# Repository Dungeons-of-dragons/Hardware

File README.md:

# Hardware

This repo holds our PCB schematics and PCB design and is used for version control of PCBs.

## PCB design directory

The directory holds the **Project_Libraries** and schematics and PCB design.

Thr Project Libraries folder contains custom symbols and footprints of the sensors used. The component used can be found within the Home.csv file. that is the BOM.

## Bill of Materials

The components needed to replicate this PCB and project are:

- 1 ESP32 DEVKIT V1 microcontroller
- 2 LM2596 Buck converters
- 1 Buzzer
- 1 RGB LED (or three  LEDs, note to add resistors if used)
- 7 2-pin screw terminal blocks
- 2 3-pin screw terminal blocks
- 1 ACS712_5B sensor (current sensor)
- 1 DHT11 sensor (Temperature and Humidity)
- 1 PIR sensor (motion sensor)
- 1 MQ2 sensor (gas sensor)
- 1 Relay

There are components attatched to the PCB externally:

- 1 Fan
- 1 LCD with I2C
- 1 EM Lock
- 1  RFID card reader (RFC522)
- 12V power supply
- 1 Relay module

## The PCB Schematic

### Power Distribution

Components used had different power needs. The use of two buck converters is to ensure that the components that were powered by 3.3V, 5V and 12V are catered for.
An external power source of 12V is used to power the PCB through the power terminal that is the power input of the PCB. Power is the distributed from there.

### External connections

Terminals are used as input and output to components used externally such as the RFID card reader, Electromagnetic lock, fan and LCD. The ACS terminal is used as input of the voltage to be measured by the ACS712 sensor.

## PCB

### Layers of the PCB

Courtyard - Boundary of a footprint.
Fab - Stands for . It gives more information on fabrication to the manufacturer.
Adhesive - Layer to glue components that need to be put in place.
Paste - Layer to apply solder mask onto a PCB.
Silkscreen - Layer to label components and print onto.
Mask - Protects the PCB circuit adn insulates the copper from oxidation.
Copper layer - where copper routes are made and grounding places are set.

As we were fabricating ourselves, some of the layers were not needed, such as mask, fab. adhesive.

### Constraints set up

1. Minimum clearance - this is the minimum distance between 2 tracks. Too small of clearance and tracks might end up being short circuited. 0.15 is the standard requirement for the PCB.
2. Track width - this refers to the thickness of tracks. Small tracks may cause open circuits in the PCB and therefore is discouraged. The amount of current drawn by the components is a factor that should be considered. however, overall, 0.15 is good practice. The power tracks and signal tracks have different sizes due to the amount of current drawn. The 12V power tracks are thicker as they carry more current compared to ther other tracks.
3. Minimum connection width - this refers to the minimum connection between 2 components of the width is less than threshold, connection may be broken.
Kicad provides a track width calculator, we set the 12V tracks to carry 1A of current and the other tracks carrying less that 1A.

4. Minimum through hole - This is the minimum diameter of a trhough hole pin. 0.8 is set because the least strongest drill bit we can use without breaking is 0.8mm.

5. Copper to edge clearance - this is the least distance that can be there between a copper track and the edge cut. A small distance may lead to the copper tracks being cut out during fabrication of the PCB, hence a suitable legnth should be set between them.

### PCB Routing

The PCB routing was done manually to ensure there were no errors. The shortest paths were used where possible, however, due to arrangement of components and connections, other alternative longer paths were taken to enable connection of all paths. The routing is only on the front side of the copper clad so as to easen DIY manufacture. aligning components on both sides would make aligning of tracks holes hard, hence one side is more efficient.
The arrangement was factored by power requirements, whether the components are analog or digital and specific positioning of some components. Components that needed 5V power were grouped together and components that needed 3.3V power were grouped together. Analog components and digital components were grouped together, respectively to prevent crossing of lines during routing. The terminal blocks were set to the edge of the PCB to ease connection to external components. The ESP32 microcontroller was set in the middle of the board to easen access of all sensors and terminal blocks to it and resuce the legnth of tracks.
The tracks are filleted to reduce inductance and therefore reducing cases of reflection caused by sharp corners in the tracks by sharp edges.
The tracks used are 1.7mm thick for power tracks and 1mm thick for signal tracks. The power tracks are thicker as they carry more current and the thick tracks are to ensure that the tracks don't break when etching. They also have less heat dissipation. The other tracks are narrower to ease routing and control impedence.

### 3D PCB

After routing, the final PCB would be expected to look like this:

This is the desired output after fabrication.

To prepare for fabrication, we plot the PCB layers and ensure that the edge cut is in each plot.

Plotting:

The front copper layer is the one we need:

## Fabrication

### Components needed for fabrication

- HCL
- Hydrogen Peroxide
- Acetone
- Glossy paper
- Laser Printer
- 0.8mm drill bit
- 1.0mm drill bit
- PCB drill
- Rough sand paper or a substitute(we used steel wool)
- Smooth sand paper or substitute( we used supabrite)

### Procedure

#### Etching Process

1. Print the PCB plotted design on a glossy paper using a laser printer.
2. Cut the required dimensions of the PCB onto the copper clad and file the edges to ensure a smooth
and even edge.
3. Sand down the copper clad with fine sand paper until its shiny. Ensure all grease and fingerprints is
off of it as this may make it difficult for the toner to transfer.
4. Place the glossy paper on the copper clad, toner sider down and iron it with clothe iron for 50
minutes. Make sure heat is evenly distributed, especially with the edges and corners
5. Wait for it to cool before removing the glossy paper.
6. Once cooled, remove the glossy paper and be gentle with places where the paper is still stuck. The
toner is transferred and is now ready for etching.
7. In the case of a two-sided PCB, follow the stpes from 3-6 on the other side of the PCB. Ensure it is
well aligned with the holes at the top.
8. Use a solution of hydrogen peroxide and HCL to etch in the ratio of 2:1. For safety pour the
hydrogen peroxide into HCL, and ensure to wear a mask during the etching process as dangerous
fumes are emitted.
9. Gently place the PCB into the solution using a pliers, close the lid of the container and shake it
gently to ensure all exposed copper is eroded.
10. Open the container and occasionally turn the PCB until all the exposed copper is eroded.
11. Once etching is complete rinse the copper clad with water nd pour acetone on the PCB while
scrubbing out the toner. The parts covered with the toner expose the wanted copper.
12. Using a multimeter check for continuity of the tracks.
13. Fix discontinued tracks with soldering wire

#### Assembly of the PCB

14. Solder the components onto their respective footprints
15. Test PCB with the firmware.

## Challenges

1. On our first attempt, we made our copper tracks to thin. Below is the plot:

After etching this was the result:

As seen above, some of the tracks are broken as they are too thin that they're disconnected.
2. Breaking of drill bits while drilling. The 0.8mm drill bit proved to be too delicate and thus we changed all footprints to have a hole diameter of 1.0mm so as to use the 1.0mm.

## Recommendations

 1. Read documentation of the microcontroller in use and components to ensure you meet their requirements.
 2. Use a stronger and more durable drill bit.

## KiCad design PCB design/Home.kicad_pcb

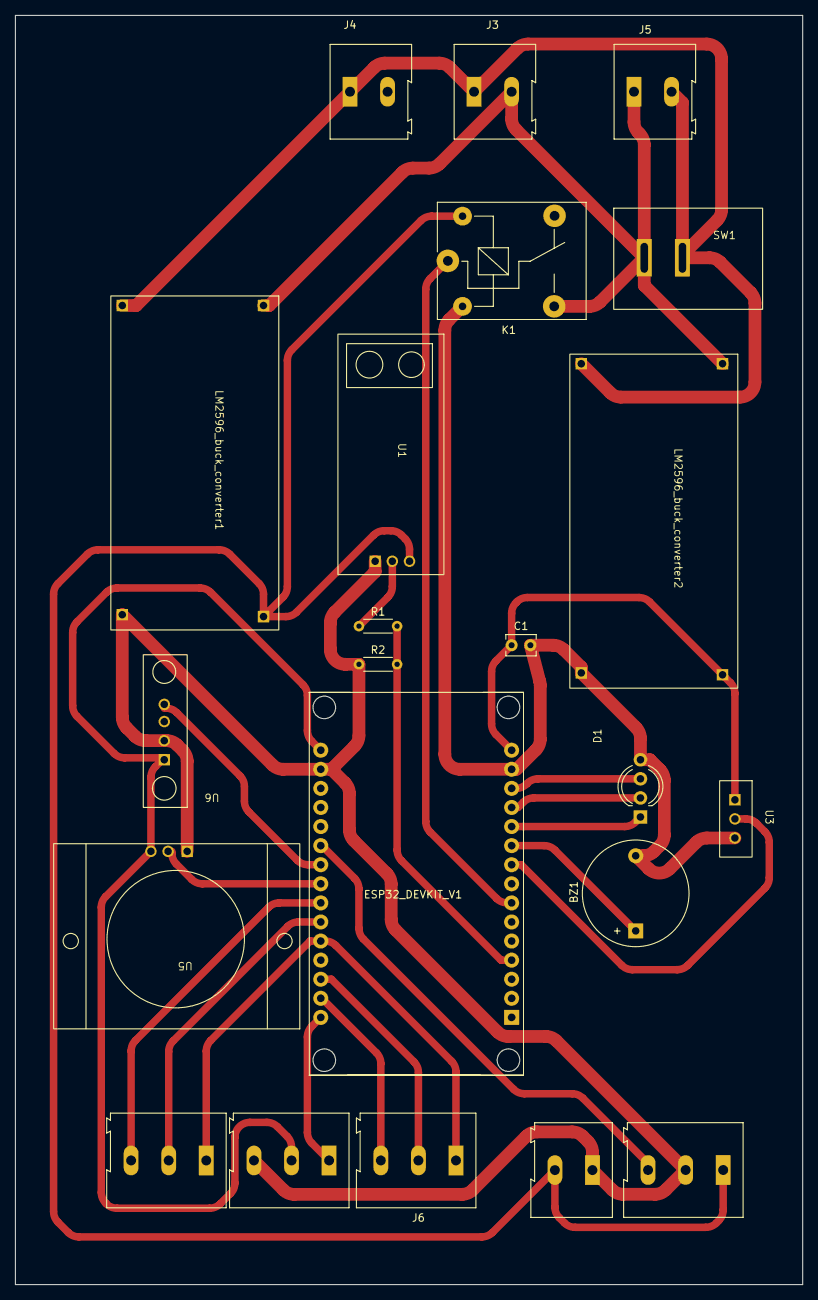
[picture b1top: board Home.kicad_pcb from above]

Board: 2 copper layers, 104.8 x 168.9 mm, 22 parts (0 on the bottom side), 23 nets.

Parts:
BZ1: Buzzer; Buzzer_D14mm_H7mm_P10mm
C1: C; C_Disc_D3.8mm_W2.6mm_P2.50mm
D1: LED_RGBK; RGB_LED
ESP32_DEVKIT_V1: MODULE_ESP32_DEVKIT_V1
J1: Fan; TerminalBlock_Altech_AK300-3_P5.00mm
J2: LCD; TerminalBlock_Altech_AK300-2_P5.00mm
J3: EM lock; TerminalBlock_Altech_AK300-2_P5.00mm
J4: ACS712 Signal; TerminalBlock_Altech_AK300-2_P5.00mm
J5: Power In; TerminalBlock_Altech_AK300-2_P5.00mm
J6: LCD; TerminalBlock_Altech_AK300-3_P5.00mm
J7, J8: RFID; TerminalBlock_Altech_AK300-3_P5.00mm
K1: SANYOU_SRD_Form_C; Relay_SPDT_SANYOU_SRD_Series_Form_C
LM2596_buck_converter1: 5V; LM2596_module
LM2596_buck_converter2: 3.3V; LM2596_module
R1, R2: R; R_Axial_DIN0204_L3.6mm_D1.6mm_P5.08mm_Horizontal
SW1: SW_SPST; SPST - KCD1-11
U1: ACS712; ACS712_5B
U3: DHT11; DHT11_KY-015
U5: PIR; PIR_HC-S501
U6: MQ2

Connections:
3V3: ESP32_DEVKIT_V1.16 (3.3V), J8.2, U5.3 (VCC), U6.1 (VCC)
+3.3V: C1.1, ESP32_DEVKIT_V1.15 (VIN), LM2596_buck_converter2.3 (+OUT), U3.1 (VCC)
+5V: J1.1, J2.2, K1.5, LM2596_buck_converter1.3 (+OUT), U1.1 (VCC)
+12V: J3.2, J5.1, K1.3, LM2596_buck_converter1.1 (+IN), LM2596_buck_converter2.1 (+IN), SW1.1 (A)
-12V: J3.1, J4.1, J5.2, LM2596_buck_converter1.2 (-IN), LM2596_buck_converter2.2 (-IN), SW1.2 (B)
ACS: ESP32_DEVKIT_V1.4 (GPIO34), R1.2, R2.2
BLUE: D1.2 (GA), ESP32_DEVKIT_V1.12 (GPIO12)
BUZZ: BZ1.1 (-), ESP32_DEVKIT_V1.10 (GPIO27)
DHT: ESP32_DEVKIT_V1.9 (GPIO26), U3.2 (IO)
Fan: ESP32_DEVKIT_V1.21 (GPIO16/RXD_2), J1.3
GND: BZ1.2 (+), C1.2, D1.4 (K), ESP32_DEVKIT_V1.14 (GND), ESP32_DEVKIT_V1.17 (GND), J1.2, J2.1, J8.3, K1.2, LM2596_buck_converter1.4 (-OUT), LM2596_buck_converter2.4 (-OUT), R2.1, U1.3 (GND), U3.3 (GND), U5.1 (GND), U6.2 (GND)
GREEN: D1.3 (BA), ESP32_DEVKIT_V1.13 (GPIO13)
MISO: ESP32_DEVKIT_V1.25 (GPIO19/MISO), J7.2
MOSI: ESP32_DEVKIT_V1.30 (GPIO23/MOSI), J8.1
MQ2: ESP32_DEVKIT_V1.22 (GPIO17/TXD_2), U6.4 (AO)
unnamed: R1.1, U1.2 (OUT)
PIR: ESP32_DEVKIT_V1.23 (GPIO5/SS), U5.2 (OUT)
RED: D1.1 (RA), ESP32_DEVKIT_V1.11 (GPIO14)
RELAY: ESP32_DEVKIT_V1.7 (GPIO33), K1.1
RESET: ESP32_DEVKIT_V1.28 (GPIO1/TXD0), J6.2
SCK: ESP32_DEVKIT_V1.24 (GPIO18/SCK), J7.3
SCL: ESP32_DEVKIT_V1.29 (GPIO22/SCL), J6.3
SDA: ESP32_DEVKIT_V1.26 (GPIO21/SDA), J6.1, J7.1

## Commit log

2023-11-21 PCB schematic
2023-11-22 complete symbols and schematic
2023-11-22 complete schematic
2023-11-22 footprints complete
2023-11-22 PCB circuit to be completed
2023-11-23 PCB routed
2023-11-23 removed unnecesarry files
2023-11-24 PCB rerouting, with warnings
2023-11-24 complete pcb without warnings
2023-11-25 added relay
2023-11-26 edited relay
2023-11-26 Readme updated
2023-11-26 added plots
2023-11-27 corrected plots
2023-11-29 PCB with thicker tracks
2023-11-29 final edits
2023-11-29 Readme and pictures updated
2023-11-29 radme
2023-11-29 readme
